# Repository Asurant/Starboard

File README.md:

# Starboard
The Starboard is a 4 layer USB C devboard that I made using a PY32 chip. It has two 9-pin headers, each offering VBUS, +3.3V, and GND along with 4 IO pins, NRST, and BOOT. Along with this it offers the ability to use a microSD to store code for the devboard. Currently I have not made the physical pcb for this. Currently only the files exist.
| Top View | Bottom View |
|---|---|
|  | 
 |

## Schematic

## PCB

## BOM
(Please note prices take into factor the minimum buy amounts for each part)
### 1 PCB
| Part                   | Quantity | Price  | LCSC Number |
|------------------------|----------|--------|-------------|
| Capacitors (1uF)       | 4        | $0.42  | C116352     |
| Capacitors (100nF)     | 4        | $0.13  | C344180     |
| Micro SD Slot          | 1        | $0.63  | C393941     |
| 1x09 Pin Header        | 2        | $0.46  | C492408     |
| Resistor (5.1k)        | 2        | $0.22  | C2930296    |
| Resistor (10k)         | 3        | $0.17  | C54921249   |
| Tactile Switch         | 4        | $0.53  | C720477     |
| CH340N                 | 1        | $0.68  | C2977777    |
| ME6211A33M3G-N         | 1        | $0.63  | C168807     |
| PY32F002BF15P6TR       | 1        | $0.93  | C22438998   |
| USB C                  | 1        | $1.41  | C2765186    |
| PCB                    | 5        | $7.00  |             |
| Total Without Shipping |          | $13.21 |             |
| Shipping               |          | $19.20 |             |
| Total With Shipping    |          | $32.40 |             |
### 5 PCBs
| Part                   | Quantity | Price  | LCSC Number |
|------------------------|----------|--------|-------------|
| Capacitors (1uF)       | 20       | $0.42  | C116352     |
| Capacitors (100nF)     | 20       | $0.13  | C344180     |
| Micro SD Slot          | 5        | $0.63  | C393941     |
| 1x09 Pin Header        | 10       | $0.46  | C492408     |
| Resistor (5.1k)        | 10       | $0.22  | C2930296    |
| Resistor (10k)         | 15       | $0.17  | C54921249   |
| Tactile Switch         | 20       | $1.06  | C720477     |
| CH340N                 | 5        | $3.39  | C2977777    |
| ME6211A33M3G-N         | 5        | $0.63  | C168807     |
| PY32F002BF15P6TR       | 5        | $0.93  | C22438998   |
| USB C                  | 5        | $1.41  | C2765186    |
| PCB                    | 5        | $7.00  |             |
| Total Without Shipping |          | $16.45 |             |
| Shipping               |          | $19.20 |             |
| Total With Shipping    |          | $35.65 |             |

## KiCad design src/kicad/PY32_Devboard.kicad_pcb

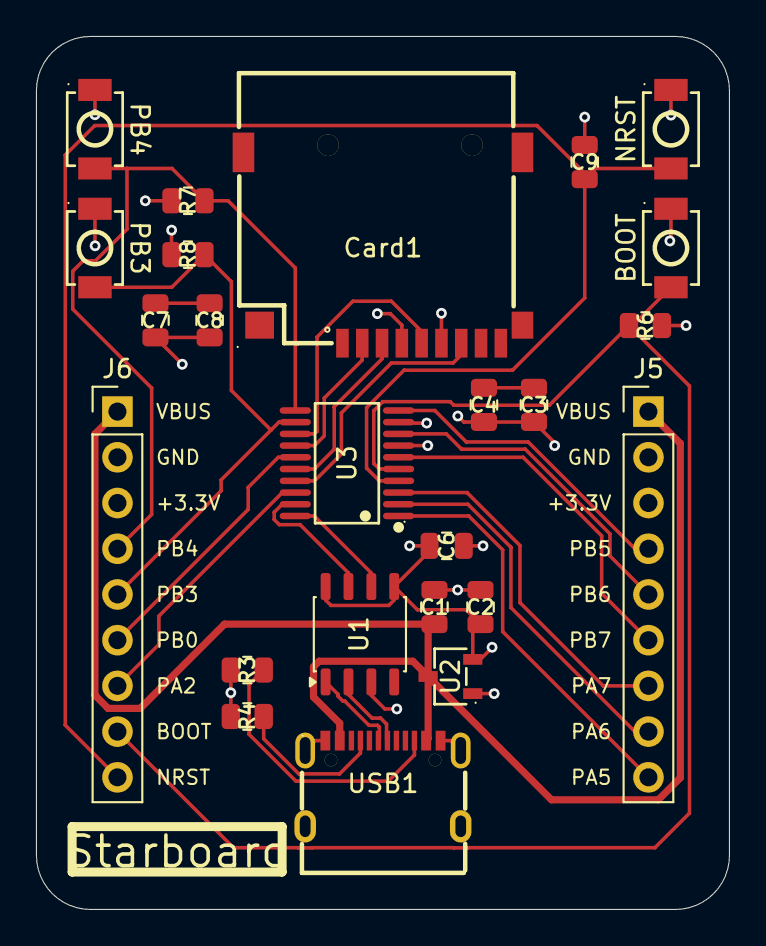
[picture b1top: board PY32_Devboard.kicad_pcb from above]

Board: 4 copper layers, 38.5 x 48.5 mm, 24 parts (0 on the bottom side), 27 nets.

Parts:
BOOT: BOOT; SW-SMD_L3.9-W3.0-P4.45
C1, C2, C3, C8: 1uF; C_0805_2012Metric
C4, C6, C7, C9: 100nF; C_0805_2012Metric
Card1: TF PUSH; TF-SMD_TF-PUSH
J5, J6: Conn_01x09; PinHeader_1x09_P2.54mm_Vertical
NRST: RESET; SW-SMD_L3.9-W3.0-P4.45
PB3: PB1; SW-SMD_L3.9-W3.0-P4.45
PB4: PB0; SW-SMD_L3.9-W3.0-P4.45
R3, R4: 5.1k; R_0805_2012Metric
R6, R7, R8: 10k; R_0805_2012Metric
U1: CH340N; JEITA_SOIC-8_3.9x4.9mm_P1.27mm
U2: ME6211A33M3G-N; SOT-23-3_L2.9-W1.6-P1.90-LS2.8-BR
U3: PY32F002BF15P6TR; TSSOP-20_L6.5-W4.4-P0.65-LS6.4-BL
USB1: TYPE-C 16PIN 2MD; USB-C-SMD_TYPE-C-16PIN-2MD-073

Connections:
+3.3V: BOOT.2, C2.1, C3.1, C4.1, C6.1, C7.1, C8.1, Card1.4 (VDD), J5.3, J6.3, R7.1, R8.1, U1.5 (VCC), U1.8 (V3), U2.2 (VOUT), U3.9 (VCC)
/BOOT: BOOT.1, J6.8, R6.1, U3.5 (PC1)
/D+: U1.1 (UD+), USB1.A6 (Dp1), USB1.B6 (Dp2)
/D-: U1.2 (UD-), USB1.A7 (Dn1), USB1.B7 (Dn2)
/NRST: C9.1, J6.9, NRST.1, U3.4 (PC0-NRST)
/PA0: Card1.3 (CMD), U3.16 (PA0)
/PA1: Card1.7 (DAT0), U3.17 (PA1)
/PA2: J6.7, U3.18 (PA2-SWC)
/PA3: U1.7 (RXD), U3.19 (PA3)
/PA4: U1.6 (TXD), U3.20 (PA4)
/PA5: J5.9, U3.1 (PA5)
/PA6: J5.8, U3.2 (PA6)
/PA7: J5.7, U3.3 (PA7)
/PB0: J6.6, U3.15 (PB0)
/PB1: Card1.2 (CD/DAT3), U3.14 (PB1)
/PB2: Card1.5 (CLX), U3.13 (PB2)
/PB3: J6.5, PB3.1, R8.2, U3.12 (PB3)
/PB4: J6.4, PB4.1, R7.2, U3.11 (PB4)
/PB5: J5.4, U3.10 (PB5)
/PB6: J5.5, U3.8 (PB6-SWD)
/PB7: J5.6, U3.6 (PB7)
GND: C1.2, C2.2, C6.2, C9.2, Card1.6 (VSS), J5.2, J6.2, NRST.2, PB3.2, PB4.2, R3.2, R4.2, R6.2, U1.3 (GND), U2.1 (VSS), U3.7 (VSS), USB1.13 (EH), USB1.14 (EH), USB1.A1B12 (GND), USB1.B1A12 (GND)
unnamed: C3.2, C4.2
unnamed: C7.2, C8.2
unnamed: R4.1, USB1.A5 (CC1)
unnamed: R3.1, USB1.B5 (CC2)
VBUS: C1.1, J5.1, J6.1, U2.3 (VIN), USB1.A4B9 (VBUS), USB1.B4A9 (VBUS)

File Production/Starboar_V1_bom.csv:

Designator,Footprint,Quantity,Value,LCSC Part #
BOOT,SW-SMD_L3.9-W3.0-P4.45,1,BOOT,C720477
"C1, C2, C3, C8",0805,4,1uF,C116352
"C4, C6, C7, C9",0805,4,100nF,C344180
CARD1,TF-SMD_TF-PUSH,1,TF PUSH,C393941
"J5, J6",PinHeader_1x09_P2.54mm_Vertical,2,Conn_01x09,C492408
NRST,SW-SMD_L3.9-W3.0-P4.45,1,RESET,C720477
PB3,SW-SMD_L3.9-W3.0-P4.45,1,PB1,C720477
PB4,SW-SMD_L3.9-W3.0-P4.45,1,PB0,C720477
"R3, R4",0805,2,5.1k,C2930296
"R6, R7, R8",0805,3,10k,C54921249
U1,JEITA_SOIC-8_3.9x4.9mm_P1.27mm,1,CH340N,C2977777
U2,SOT-23-3_L2.9-W1.6-P1.90-LS2.8-BR,1,ME6211A33M3G-N,C168807
U3,TSSOP-20_L6.5-W4.4-P0.65-LS6.4-BL,1,PY32F002BF15P6TR,C22438998
USB1,USB-C-SMD_TYPE-C-16PIN-2MD-073,1,TYPE-C 16PIN 2MD,C2765186
